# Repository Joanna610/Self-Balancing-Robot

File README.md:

# Self_Balancing_Robot

This project is still in development !!!

The projects include code for Arduino. It collects data from the acceleromiter MPU6050 and modifies them accordingly. The code also turn on and off the motors with PWM. It can do this thanks to H bridge - L293D. The robot try to stabilize itself due to implemented PID algorithm.

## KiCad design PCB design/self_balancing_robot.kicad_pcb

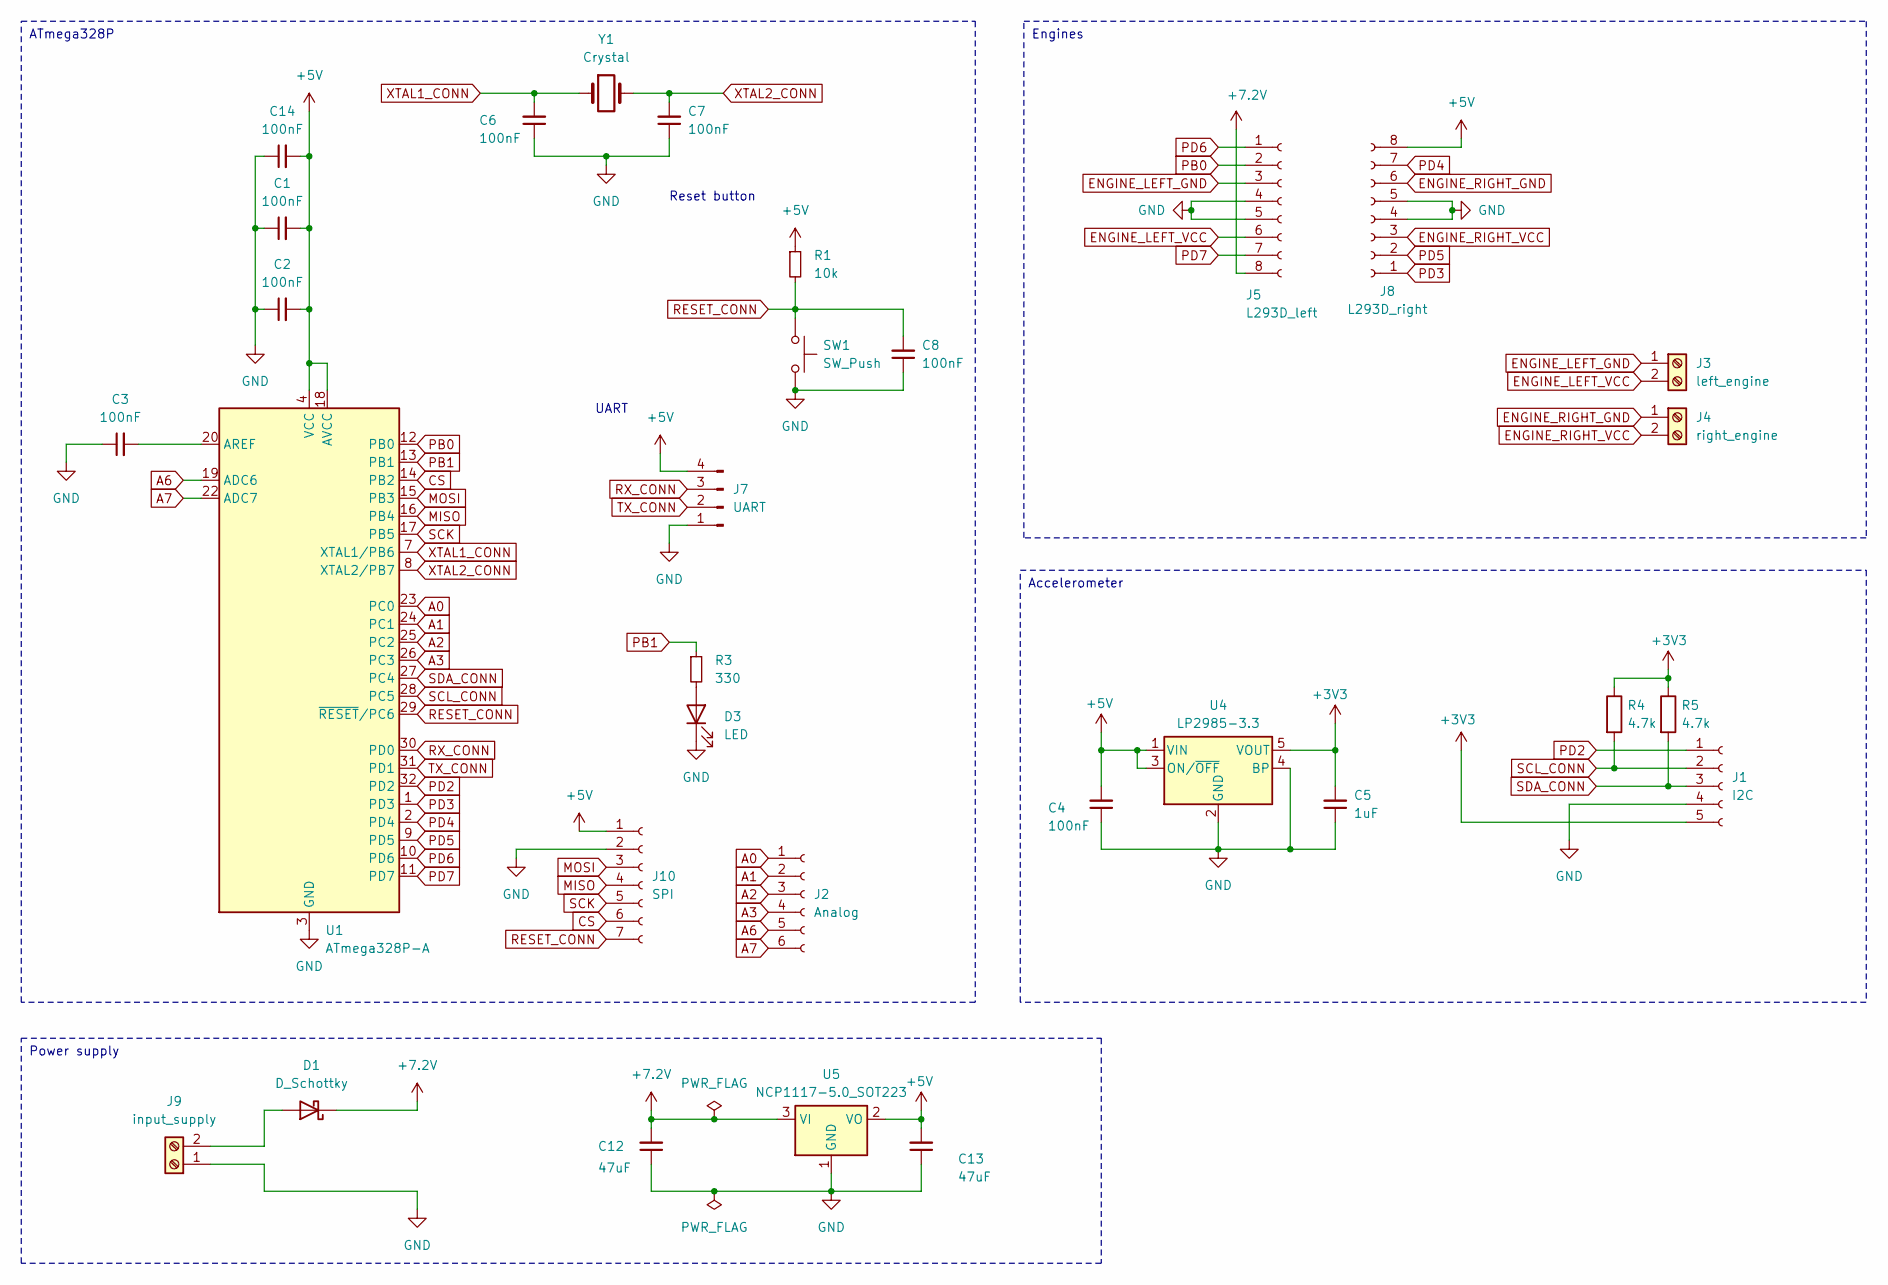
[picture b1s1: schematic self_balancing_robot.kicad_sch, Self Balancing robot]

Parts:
C1, C2, C3, C4, C6, C7, C8, C14: 100nF; C_0805_2012Metric
C5: 1uF; C_0805_2012Metric
C12, C13: 47uF; C_0805_2012Metric
D1: D_Schottky; R_Axial_DIN0207_L6.3mm_D2.5mm_P7.62mm_Horizontal
D3: LED; LED_1206_3216Metric
J1: I2C; PinSocket_1x05_P2.54mm_Vertical
J2: Analog; PinSocket_1x06_P2.54mm_Vertical
J3: left_engine; TE_826576-2_1x02_P3.96mm_Vertical
J4: right_engine; TE_826576-2_1x02_P3.96mm_Vertical
J5: L293D_left; PinSocket_1x08_P2.54mm_Vertical
J7: UART; PinHeader_1x04_P2.54mm_Vertical
J8: L293D_right; PinSocket_1x08_P2.54mm_Vertical
J9: input_supply; TE_826576-2_1x02_P3.96mm_Vertical
J10: SPI; PinSocket_1x07_P2.54mm_Vertical
R1: 10k; R_0805_2012Metric
R3: 330; R_0805_2012Metric
R4, R5: 4.7k; R_0805_2012Metric
SW1: SW_Push; SW_PUSH_1P1T_6x3.5mm_H5.0_APEM_MJTP1250
U1: ATmega328P-A; TQFP-32_7x7mm_P0.8mm
U4: LP2985-3.3; SOT-23-5
U5: NCP1117-5.0_SOT223; SOT-223-3_TabPin2
Y1: Crystal; Crystal_HC49-4H_Vertical

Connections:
+3V3: C5.2, J1.5, R4.1, R5.1, U4.5 (VOUT)
+5V: C1.2, C2.2, C4.2, C13.2, C14.2, J7.4, J8.8, J10.1, R1.1, U1.4 (VCC), U1.6 (VCC), U1.18 (AVCC), U4.1 (VIN), U4.3 (ON/~OFF), U5.2 (VO)
+7.2V: C12.2, D1.1 (K), J5.8, U5.3 (VI)
A0: J2.1, U1.23 (PC0)
A1: J2.2, U1.24 (PC1)
A2: J2.3, U1.25 (PC2)
A3: J2.4, U1.26 (PC3)
A6: J2.5, U1.19 (ADC6)
A7: J2.6, U1.22 (ADC7)
CS: J10.6, U1.14 (PB2)
ENGINE_LEFT_GND: J3.1, J5.3
ENGINE_LEFT_VCC: J3.2, J5.6
ENGINE_RIGHT_GND: J4.1, J8.6
ENGINE_RIGHT_VCC: J4.2, J8.3
GND: C1.1, C2.1, C3.1, C4.1, C5.1, C6.1, C7.1, C8.1, C12.1, C13.1, C14.1, D3.1 (K), J1.4, J5.4, J5.5, J7.1, J8.4, J8.5, J9.1, J10.2, SW1.2, U1.3 (GND), U1.5 (GND), U1.21 (GND), U4.2 (GND), U4.4 (BP), U5.1 (GND)
MISO: J10.4, U1.16 (PB4)
MOSI: J10.3, U1.15 (PB3)
unnamed: D1.2 (A), J9.2
unnamed: D3.2 (A), R3.2
unnamed: C3.2, U1.20 (AREF)
PB0: J5.2, U1.12 (PB0)
PB1: R3.1, U1.13 (PB1)
PD2: J1.1, U1.32 (PD2)
PD3: J8.1, U1.1 (PD3)
PD4: J8.7, U1.2 (PD4)
PD5: J8.2, U1.9 (PD5)
PD6: J5.1, U1.10 (PD6)
PD7: J5.7, U1.11 (PD7)
RESET_CONN: C8.2, J10.7, R1.2, SW1.1, U1.29 (~RESET/PC6)
RX_CONN: J7.3, U1.30 (PD0)
SCK: J10.5, U1.17 (PB5)
SCL_CONN: J1.2, R4.2, U1.28 (PC5)
SDA_CONN: J1.3, R5.2, U1.27 (PC4)
TX_CONN: J7.2, U1.31 (PD1)
XTAL1_CONN: C6.2, U1.7 (XTAL1/PB6), Y1.1
XTAL2_CONN: C7.2, U1.8 (XTAL2/PB7), Y1.2

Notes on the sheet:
Engines
ATmega328P
Accelerometer
Power supply
UART
Reset button

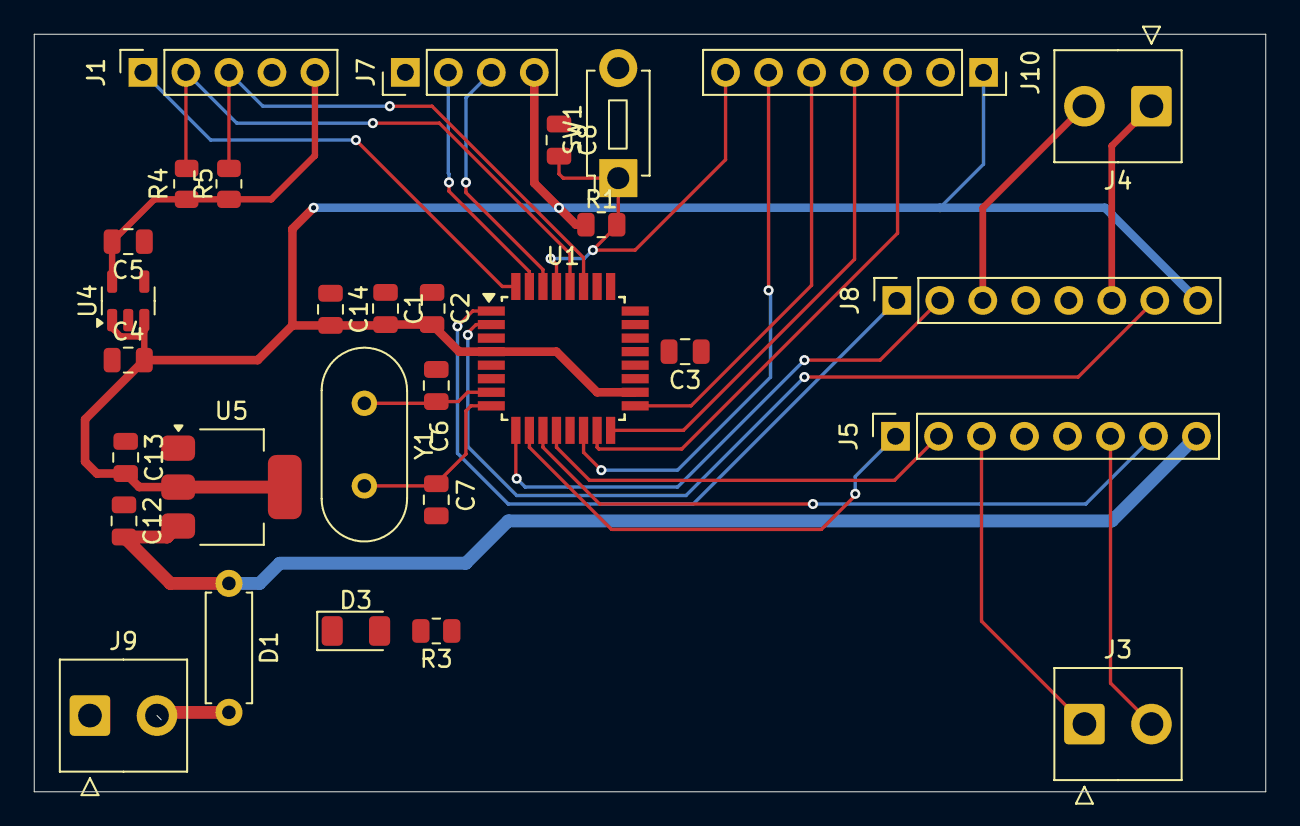
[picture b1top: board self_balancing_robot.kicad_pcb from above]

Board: 2 copper layers, 72.8 x 44.8 mm, 30 parts (0 on the bottom side), 30 nets.

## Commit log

2025-07-17 Update in PCB - almost finish version
2025-09-13 Renew PCB design - switch from atmega to avr
2025-09-14 PCB update
2025-12-29 Cleaning in files part 1
2026-02-12 New project, new me
2026-02-12 New project, new me 2
